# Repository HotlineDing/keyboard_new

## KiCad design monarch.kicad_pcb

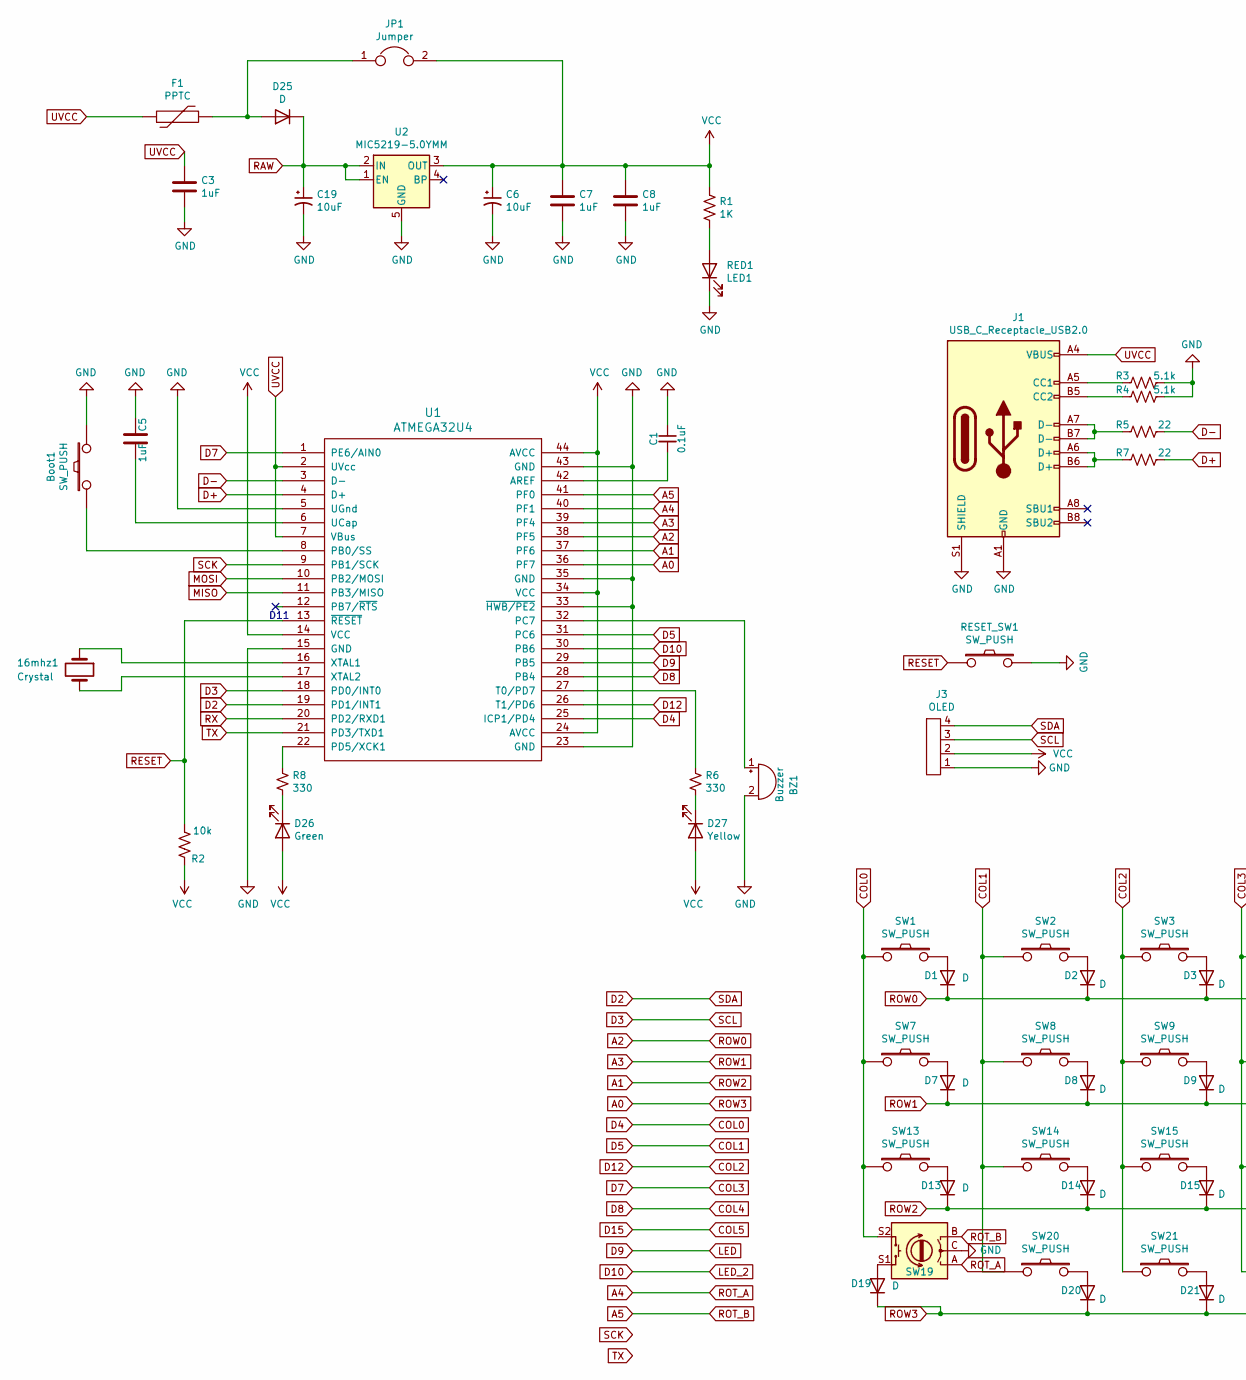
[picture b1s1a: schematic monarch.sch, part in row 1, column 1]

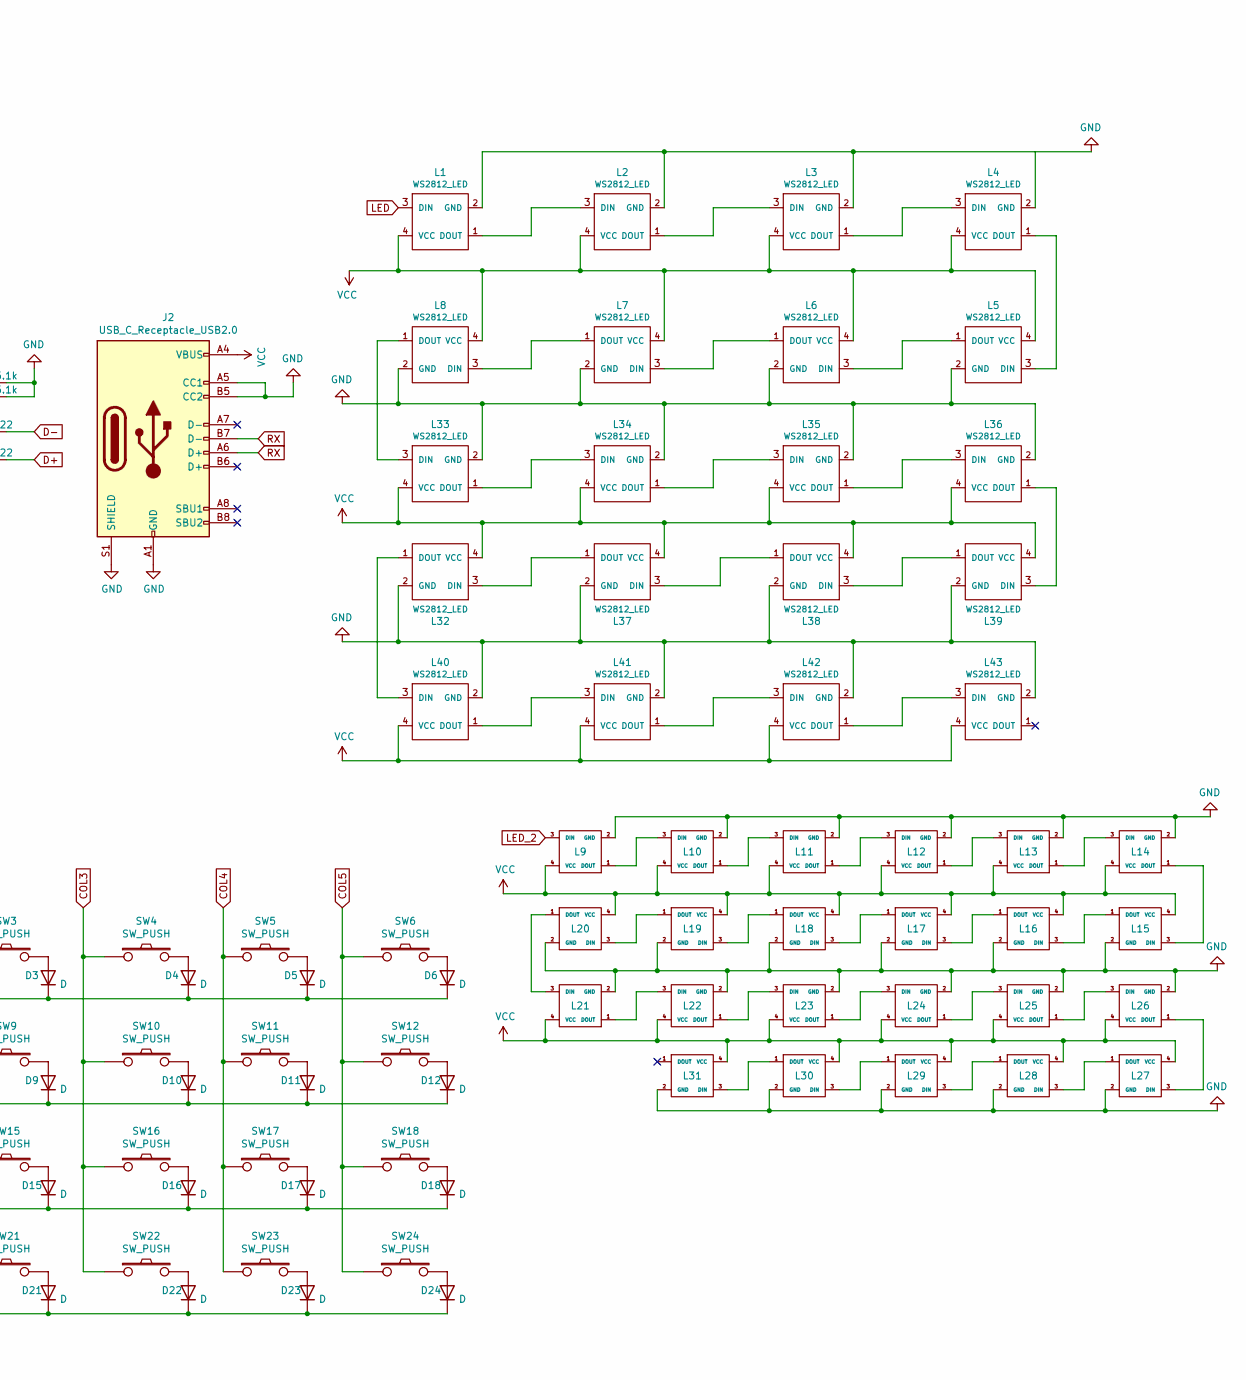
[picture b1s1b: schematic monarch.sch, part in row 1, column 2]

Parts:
16mhz1: Crystal; Crystal_HC49-4H_Vertical
BZ1: Buzzer
Boot1: SW_PUSH; SW_Push_1P1T_NO_6x6mm_H9.5mm
C1: 0.1uF; C_0805_2012Metric
C3, C5, C7, C8: 1uF; C_0805_2012Metric
C6, C19: 10uF; CP_EIA-3216-10_Kemet-I
D1, D2, D3, D4, D5, D6, D7, D8, D9, D10, D11, D12, D13, D14, D15, D16, D17, D18, D19, D20, D21, D22, D23, D24, D25: D; D_SOD-123
D26: Green; LED_D3.0mm
D27: Yellow; LED_D3.0mm
F1: PPTC; Fuse_1206_3216Metric
J1, J2: USB_C_Receptacle_USB2.0; USB_C_Receptacle_GCT_USB4085
J3: OLED; Generic_0.96in-128x64-OLED-Display-IIC
JP1: Jumper; SOLDER_JUMPER_2
L1, L2, L3, L4, L5, L6, L7, L8, L32, L33, L34, L35, L36, L37, L38, L39, L40, L41, L42, L43: WS2812_LED; WS2812B
L9, L10, L11, L12, L13, L14, L15, L16, L17, L18, L19, L20, L21, L22, L23, L24, L25, L26, L27, L28, L29, L30, L31: SK6812_mini; SK6812-MINI-E
R1: 1K; R_0805_2012Metric
R2: 10k; R_0805_2012Metric
R3, R4: 5.1k; R_0805_2012Metric
R5, R7: 22; R_0805_2012Metric
R6, R8: 330; R_0805_2012Metric
RED1: LED1; LED_D3.0mm
RESET_SW1: SW_PUSH; SW_Push_1P1T_NO_6x6mm_H9.5mm
SW1, SW2, SW3, SW4, SW5, SW6, SW7, SW8, SW9, SW10, SW11, SW12, SW13, SW14, SW15, SW16, SW17, SW18, SW20, SW21, SW22, SW23, SW24: SW_PUSH; Kailh_socket_MX
SW19: Rotary_Encoder; RotaryEncoder_EC11
U1: ATMEGA32U4; ATMEGA32U4-AU
U2: MIC5219-5.0YMM; MSOP-8_3x3mm_P0.65mm

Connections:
A0: D19.1 (K), D20.1 (K), D21.1 (K), D22.1 (K), D23.1 (K), D24.1 (K), U1.36 (PF7)
A1: D13.1 (K), D14.1 (K), D15.1 (K), D16.1 (K), D17.1 (K), D18.1 (K), U1.37 (PF6)
A2: D1.1 (K), D2.1 (K), D3.1 (K), D4.1 (K), D5.1 (K), D6.1 (K), U1.38 (PF5)
A3: D7.1 (K), D8.1 (K), D9.1 (K), D10.1 (K), D11.1 (K), D12.1 (K), U1.39 (PF4)
A4: SW19.A, U1.40 (PF1)
A5: SW19.B, U1.41 (PF0)
COL0: SW1.1, SW7.1, SW13.1, SW19.S2, U1.25 (ICP1/PD4)
COL1: SW2.1, SW8.1, SW14.1, SW20.1, U1.31 (PC6)
COL2: SW3.1, SW9.1, SW15.1, SW21.1, U1.26 (T1/PD6)
COL3: SW4.1, SW10.1, SW16.1, SW22.1, U1.1 (PE6/AIN0)
COL4: SW5.1, SW11.1, SW17.1, SW23.1, U1.28 (PB4)
COL5: SW6.1, SW12.1, SW18.1, SW24.1
D2: J3.4, U1.19 (PD1/INT1)
D3: J3.3, U1.18 (PD0/INT0)
D9: L1.3 (DIN), U1.29 (PB5)
D10: L9.3 (DIN), U1.30 (PB6)
D+: R7.1, U1.4 (D+)
D-: R5.1, U1.3 (D-)
GND: BZ1.2 (+), Boot1.2, C1.1, C3.2, C5.2, C6.2, C7.2, C8.2, C19.2, J1.A1 (GND), J1.A12 (GND), J1.B1 (GND), J1.B12 (GND), J1.S1 (SHIELD), J2.A1 (GND), J2.A5 (CC1), J2.A12 (GND), J2.B1 (GND), J2.B5 (CC2), J2.B12 (GND), J2.S1 (SHIELD), J3.1, L1.2 (GND), L2.2 (GND), L3.2 (GND), L4.2 (GND), L5.2 (GND), L6.2 (GND), L7.2 (GND), L8.2 (GND), L9.2 (GND), L10.2 (GND), L11.2 (GND), L12.2 (GND), L13.2 (GND), L14.2 (GND), L15.2 (GND), L16.2 (GND), L17.2 (GND), L18.2 (GND), L19.2 (GND), L20.2 (GND), L21.2 (GND), L22.2 (GND), L23.2 (GND), L24.2 (GND), L25.2 (GND), L26.2 (GND), L27.2 (GND), L28.2 (GND), L29.2 (GND), L30.2 (GND), L31.2 (GND), L32.2 (GND), L33.2 (GND), L34.2 (GND), L35.2 (GND), L36.2 (GND), L37.2 (GND), L38.2 (GND), L39.2 (GND), L40.2 (GND), L41.2 (GND), L42.2 (GND), L43.2 (GND), R3.1, R4.1, RED1.1 (K), RESET_SW1.2, SW19.C, U1.5 (UGnd), U1.15 (GND), U1.23 (GND), U1.33 (~HWB/PE2), U1.35 (GND), U1.43 (GND), U2.5 (GND), U2.6 (GND), U2.7 (GND), U2.8 (GND)
MISO: U1.11 (PB3/MISO)
MOSI: U1.10 (PB2/MOSI)
unnamed: 16mhz1.1, U1.16 (XTAL1)
unnamed: 16mhz1.2, U1.17 (XTAL2)
unnamed: BZ1.1 (-), U1.32 (PC7)
unnamed: Boot1.1, U1.8 (PB0/SS)
unnamed: C1.2, U1.42 (AREF)
unnamed: C5.1, U1.6 (UCap)
unnamed: D1.2 (A), SW1.2
unnamed: D2.2 (A), SW2.2
unnamed: D3.2 (A), SW3.2
unnamed: D4.2 (A), SW4.2
unnamed: D5.2 (A), SW5.2
unnamed: D6.2 (A), SW6.2
unnamed: D7.2 (A), SW7.2
unnamed: D8.2 (A), SW8.2
unnamed: D9.2 (A), SW9.2
unnamed: D10.2 (A), SW10.2
unnamed: D11.2 (A), SW11.2
unnamed: D12.2 (A), SW12.2
unnamed: D13.2 (A), SW13.2
unnamed: D14.2 (A), SW14.2
unnamed: D15.2 (A), SW15.2
unnamed: D16.2 (A), SW16.2
unnamed: D17.2 (A), SW17.2
unnamed: D18.2 (A), SW18.2
unnamed: D19.2 (A), SW19.S1
unnamed: D20.2 (A), SW20.2
unnamed: D21.2 (A), SW21.2
unnamed: D22.2 (A), SW22.2
unnamed: D23.2 (A), SW23.2
unnamed: D24.2 (A), SW24.2
unnamed: D25.2 (A), F1.2, JP1.1
unnamed: D26.1 (K), R8.2
unnamed: D27.1 (K), R6.2
unnamed: J1.A5 (CC1), R3.2
unnamed: J1.A6 (D+), J1.B6 (D+), R7.2
unnamed: J1.A7 (D-), J1.B7 (D-), R5.2
unnamed: J1.B5 (CC2), R4.2
unnamed: L1.1 (DOUT), L2.3 (DIN)
unnamed: L2.1 (DOUT), L3.3 (DIN)
unnamed: L3.1 (DOUT), L4.3 (DIN)
unnamed: L4.1 (DOUT), L5.3 (DIN)
unnamed: L5.1 (DOUT), L6.3 (DIN)
unnamed: L6.1 (DOUT), L7.3 (DIN)
unnamed: L7.1 (DOUT), L8.3 (DIN)
unnamed: L10.1 (DOUT), L11.3 (DIN)
unnamed: L9.1 (DOUT), L10.3 (DIN)
unnamed: L11.1 (DOUT), L12.3 (DIN)
unnamed: L12.1 (DOUT), L13.3 (DIN)
unnamed: L13.1 (DOUT), L14.3 (DIN)
unnamed: L14.1 (DOUT), L15.3 (DIN)
unnamed: L15.1 (DOUT), L16.3 (DIN)
unnamed: L16.1 (DOUT), L17.3 (DIN)
unnamed: L17.1 (DOUT), L18.3 (DIN)
unnamed: L18.1 (DOUT), L19.3 (DIN)
unnamed: L19.1 (DOUT), L20.3 (DIN)
unnamed: L20.1 (DOUT), L21.3 (DIN)
unnamed: L21.1 (DOUT), L22.3 (DIN)
unnamed: L22.1 (DOUT), L23.3 (DIN)
unnamed: L23.1 (DOUT), L24.3 (DIN)
unnamed: L24.1 (DOUT), L25.3 (DIN)
unnamed: L25.1 (DOUT), L26.3 (DIN)
unnamed: L26.1 (DOUT), L27.3 (DIN)
unnamed: L27.1 (DOUT), L28.3 (DIN)
unnamed: L28.1 (DOUT), L29.3 (DIN)
unnamed: L29.1 (DOUT), L30.3 (DIN)
unnamed: L30.1 (DOUT), L31.3 (DIN)
unnamed: L32.1 (DOUT), L40.3 (DIN)
unnamed: L32.3 (DIN), L37.1 (DOUT)
unnamed: L33.1 (DOUT), L34.3 (DIN)
unnamed: L8.1 (DOUT), L33.3 (DIN)
unnamed: L34.1 (DOUT), L35.3 (DIN)
unnamed: L35.1 (DOUT), L36.3 (DIN)
unnamed: L36.1 (DOUT), L39.3 (DIN)
unnamed: L37.3 (DIN), L38.1 (DOUT)
unnamed: L38.3 (DIN), L39.1 (DOUT)
unnamed: L40.1 (DOUT), L41.3 (DIN)
unnamed: L41.1 (DOUT), L42.3 (DIN)
unnamed: L42.1 (DOUT), L43.3 (DIN)
unnamed: R1.2, RED1.2 (A)
unnamed: R6.1, U1.27 (T0/PD7)
unnamed: R8.1, U1.22 (PD5/XCK1)
RAW: C19.1, D25.1 (K), U2.1 (EN), U2.2 (IN)
RESET: R2.2, RESET_SW1.1, U1.13 (~RESET)
RX: J2.A6 (D+), J2.B7 (D-), U1.20 (PD2/RXD1)
SCK: U1.9 (PB1/SCK)
TX: U1.21 (PD3/TXD1)
UVCC: C3.1, F1.1, J1.A4 (VBUS), J1.A9 (VBUS), J1.B4 (VBUS), J1.B9 (VBUS), U1.2 (UVcc), U1.7 (VBus)
VCC: C6.1, C7.1, C8.1, D26.2 (A), D27.2 (A), J2.A4 (VBUS), J2.A9 (VBUS), J2.B4 (VBUS), J2.B9 (VBUS), J3.2, JP1.2, L1.4 (VCC), L2.4 (VCC), L3.4 (VCC), L4.4 (VCC), L5.4 (VCC), L6.4 (VCC), L7.4 (VCC), L8.4 (VCC), L9.4 (VCC), L10.4 (VCC), L11.4 (VCC), L12.4 (VCC), L13.4 (VCC), L14.4 (VCC), L15.4 (VCC), L16.4 (VCC), L17.4 (VCC), L18.4 (VCC), L19.4 (VCC), L20.4 (VCC), L21.4 (VCC), L22.4 (VCC), L23.4 (VCC), L24.4 (VCC), L25.4 (VCC), L26.4 (VCC), L27.4 (VCC), L28.4 (VCC), L29.4 (VCC), L30.4 (VCC), L31.4 (VCC), L32.4 (VCC), L33.4 (VCC), L34.4 (VCC), L35.4 (VCC), L36.4 (VCC), L37.4 (VCC), L38.4 (VCC), L39.4 (VCC), L40.4 (VCC), L41.4 (VCC), L42.4 (VCC), L43.4 (VCC), R1.1, R2.1, U1.14 (VCC), U1.24 (AVCC), U1.34 (VCC), U1.44 (AVCC), U2.3 (OUT)

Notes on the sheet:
D11

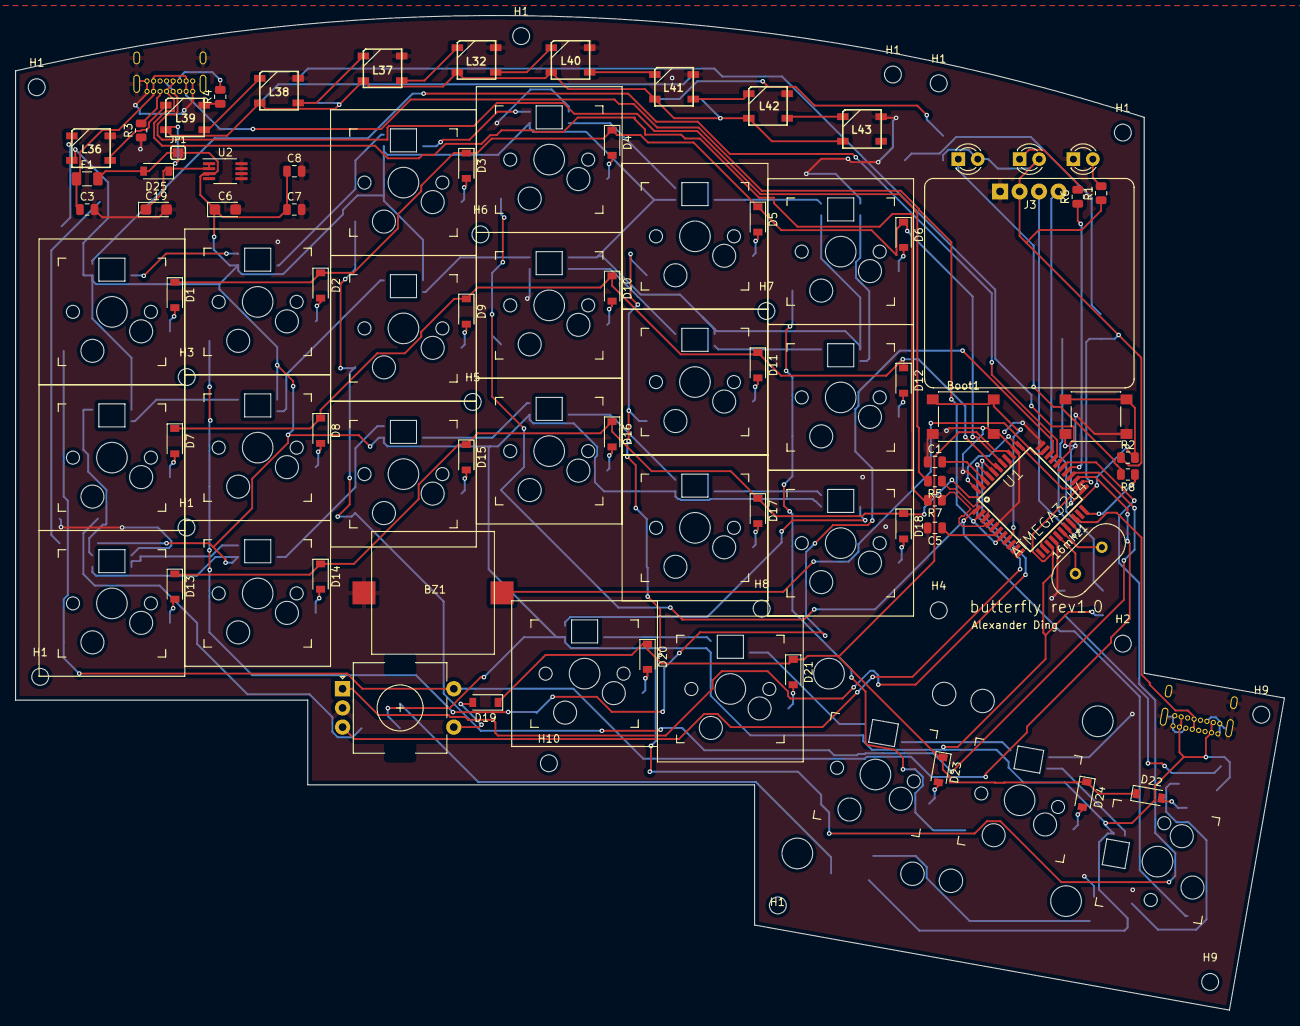
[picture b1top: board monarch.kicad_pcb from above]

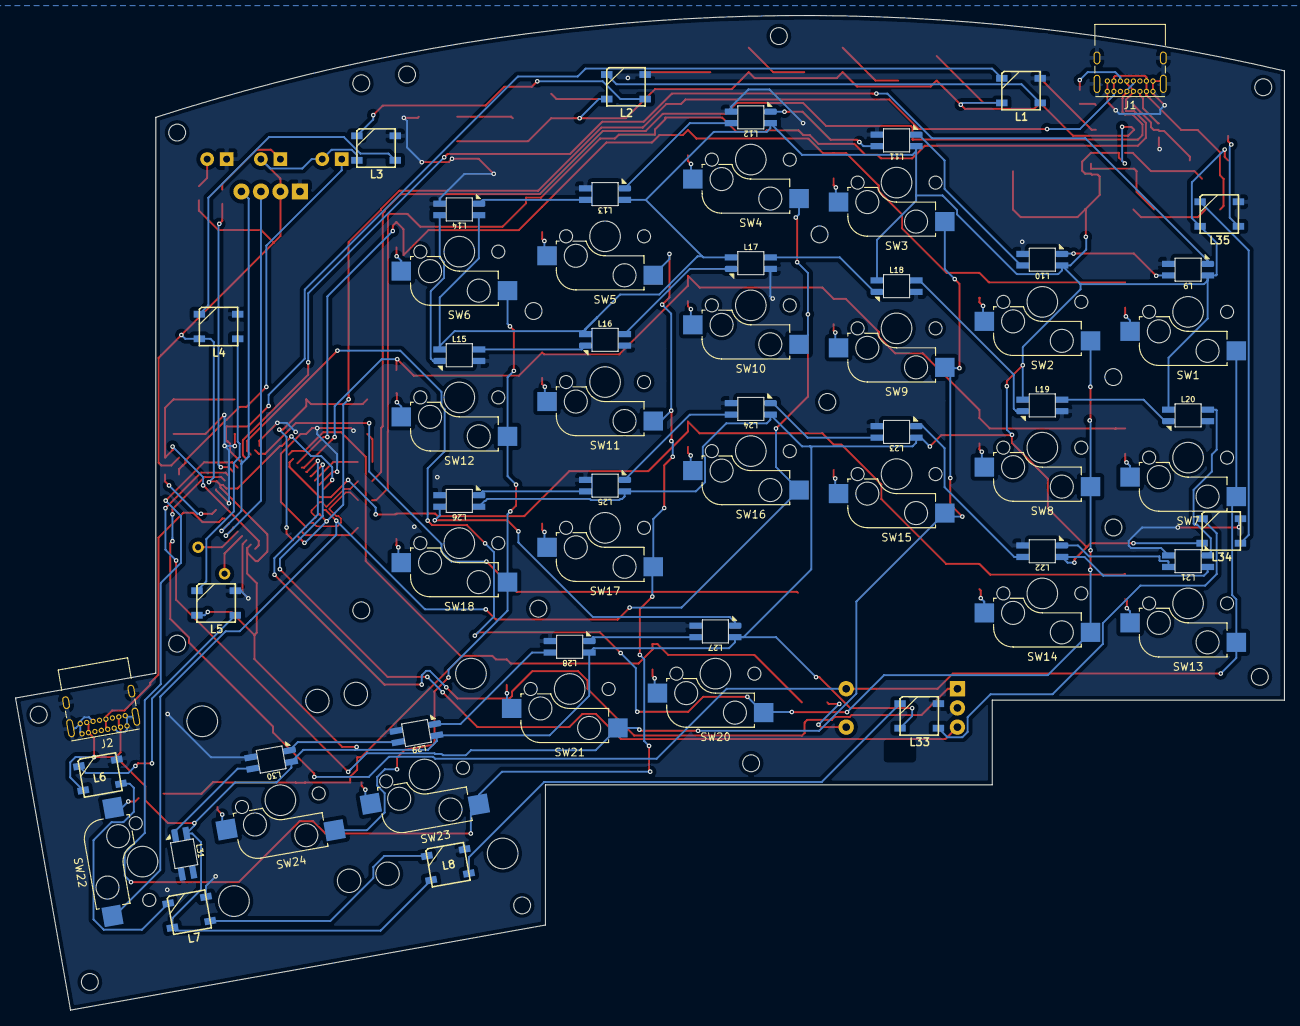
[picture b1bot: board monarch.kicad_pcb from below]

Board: 2 copper layers, 165.4 x 129.6 mm, 140 parts (36 on the bottom side), 105 nets.

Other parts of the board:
H1, H1#2, H1#3, H1#4, H1#5, H1#6, H1#7, H1#8, H2, H3, H4, H5, H6, H7, H8, H9, H9#2, H10: Hole; MountingHole_2.2mm_M2
Kailh PG1350: Choc; Kailh-PG1350-1.5u

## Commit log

2021-03-18 init commit
2021-03-20 schematic done -ish?
2021-03-22 schematic pre-final
2021-03-24 schematic final_1
2021-04-03 schematic final_2
2021-04-04 schematic final_3
2021-04-12 schematic final_4
2021-04-13 monarch update
2021-04-14 pre routing/tracing
2021-04-16 start routing
2021-04-16 plate edge case
2021-04-17 routing almost complete
2021-04-18 rerouting v2
2021-04-18 rerouting 0 unrouted
2021-04-23 pre tht crystal
2021-04-30 final routing v2
2021-05-05 logo and updating JLB components
2021-05-07 left side completed
